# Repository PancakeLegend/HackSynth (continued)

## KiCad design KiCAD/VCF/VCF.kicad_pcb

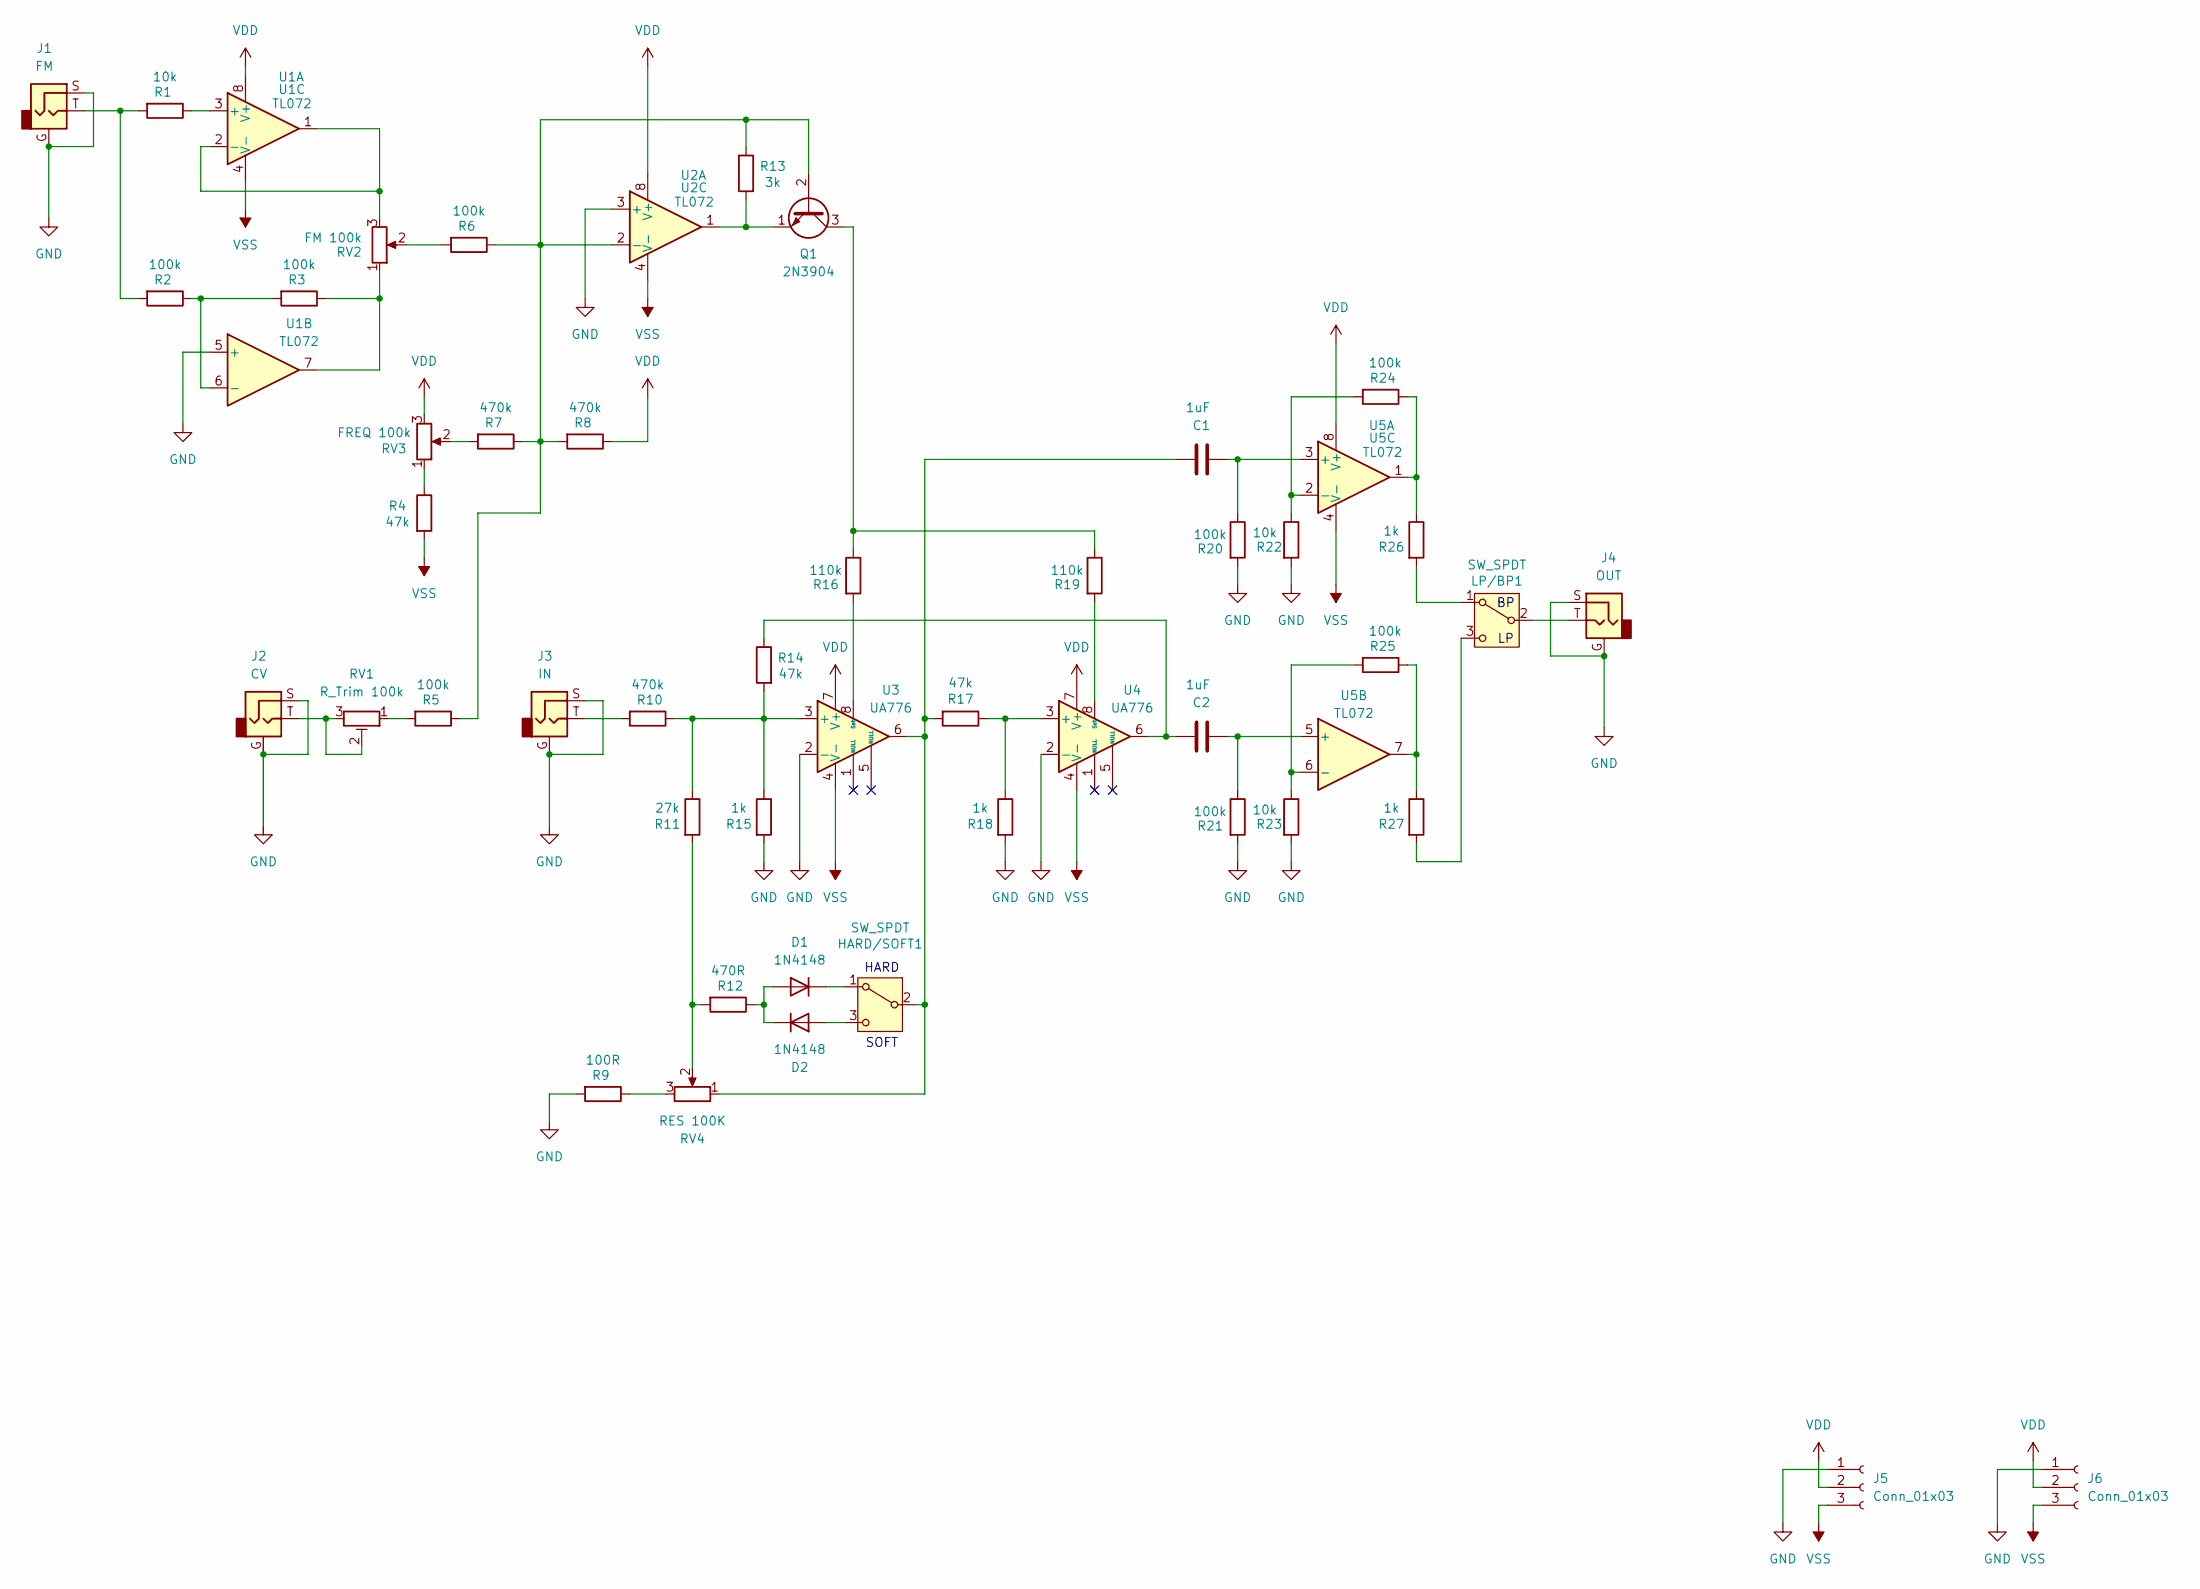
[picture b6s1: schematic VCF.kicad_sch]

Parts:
C1, C2: 1uF; C_Ceramic_D4.5mm_P5.00mm
D1, D2: 1N4148; D_DO-35_SOD27_P7.62mm_Horizontal
HARD/SOFT1: SW_SPDT; Switch SPDT - MTS-102
J1: FM; Jack_3.5mm
J2: CV; Jack_3.5mm
J3: IN; Jack_3.5mm
J4: OUT; Jack_3.5mm
J5, J6: Conn_01x03; JST_PH_S3B-PH-K_1x03_P2.00mm_Horizontal
LP/BP1: SW_SPDT; Switch SPDT - MTS-102
Q1: 2N3904; J172_TO-92_Inline - Handsolder
R1, R22, R23: 10k; R_Axial_DIN0207_L6.3mm_D2.5mm_P7.62mm_Horizontal
R2, R3, R5, R6, R20, R21, R24, R25: 100k; R_Axial_DIN0207_L6.3mm_D2.5mm_P7.62mm_Horizontal
R4, R14, R17: 47k; R_Axial_DIN0207_L6.3mm_D2.5mm_P7.62mm_Horizontal
R7, R8, R10: 470k; R_Axial_DIN0207_L6.3mm_D2.5mm_P7.62mm_Horizontal
R9: 100R; R_Axial_DIN0207_L6.3mm_D2.5mm_P7.62mm_Horizontal
R11: 27k; R_Axial_DIN0207_L6.3mm_D2.5mm_P7.62mm_Horizontal
R12: 470R; R_Axial_DIN0207_L6.3mm_D2.5mm_P7.62mm_Horizontal
R13: 3k; R_Axial_DIN0207_L6.3mm_D2.5mm_P7.62mm_Horizontal
R15, R18, R26, R27: 1k; R_Axial_DIN0207_L6.3mm_D2.5mm_P7.62mm_Horizontal
R16, R19: 110k; R_Axial_DIN0207_L6.3mm_D2.5mm_P7.62mm_Horizontal
RV1: R_Trim 100k; TrimPot_Bourns_3339S_Horizontal
RV2: FM 100k; Potentiometer_Alps_RK09K_Horizontal
RV3: FREQ 100k; Potentiometer_Alps_RK09K_Horizontal
RV4: RES 100K; Potentiometer_Alps_RK09K_Horizontal
U1, U2, U5: TL072; DIP-8_W7.62mm_LongPads
U3, U4: UA776; DIP-8_W7.62mm_LongPads

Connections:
GND: J1.G, J1.S, J2.G, J2.S, J3.G, J3.S, J4.G, J4.S, J5.1, J6.1, R9.2, R15.2, R18.2, R20.2, R21.2, R22.2, R23.2, U1.5 (+), U2.3 (+), U3.2 (-), U4.2 (-)
unnamed: C2.1, R14.1, U4.6
unnamed: D1.2 (A), D2.1 (K), R12.1
unnamed 3: D1.1 (K), HARD/SOFT1.1 (A); also elsewhere on the board
unnamed 4: D2.2 (A), HARD/SOFT1.3 (C); also elsewhere on the board
unnamed 5: C1.1, HARD/SOFT1.2 (B), R17.2, RV4.1, U3.6; also elsewhere on the board
unnamed: J1.T, R1.2, R2.2
unnamed: J2.T, RV1.2, RV1.3
unnamed: J3.T, R10.2
unnamed 9: LP/BP1.1 (A), R26.2; also elsewhere on the board
unnamed 10: J4.T, LP/BP1.2 (B); also elsewhere on the board
unnamed 11: LP/BP1.3 (C), R27.2; also elsewhere on the board
unnamed: Q1.2 (B), R5.1, R6.1, R7.1, R8.2, R13.1, U2.2 (-)
unnamed: Q1.3 (C), R16.1, R19.1
unnamed: Q1.1 (E), R13.2, U2.1
unnamed: R3.1, RV2.1, U1.7
unnamed: R4.1, RV3.1
unnamed: R5.2, RV1.1
unnamed: R6.2, RV2.2
unnamed: R7.2, RV3.2
unnamed: R9.1, RV4.3
unnamed: R11.2, R12.2, RV4.2
unnamed: R24.1, R26.1, U5.1
unnamed: R25.1, R27.1, U5.7
unnamed: R1.1, U1.3 (+)
unnamed: RV2.3, U1.1, U1.2 (-)
unnamed: R2.1, R3.2, U1.6 (-)
unnamed: R10.1, R11.1, R14.2, R15.1, U3.3 (+)
unnamed: R16.2, U3.8 (Set)
unnamed: R17.1, R18.1, U4.3 (+)
unnamed: R19.2, U4.8 (Set)
unnamed: C1.2, R20.1, U5.3 (+)
unnamed: R22.1, R24.2, U5.2 (-)
unnamed: C2.2, R21.1, U5.5 (+)
unnamed: R23.1, R25.2, U5.6 (-)
VDD: J5.2, J6.2, R8.1, RV3.3, U1.8 (V+), U2.8 (V+), U3.7 (V+), U4.7 (V+), U5.8 (V+)
VSS: J5.3, J6.3, R4.2, U1.4 (V-), U2.4 (V-), U3.4 (V-), U4.4 (V-), U5.4 (V-)

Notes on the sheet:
SOFT
HARD

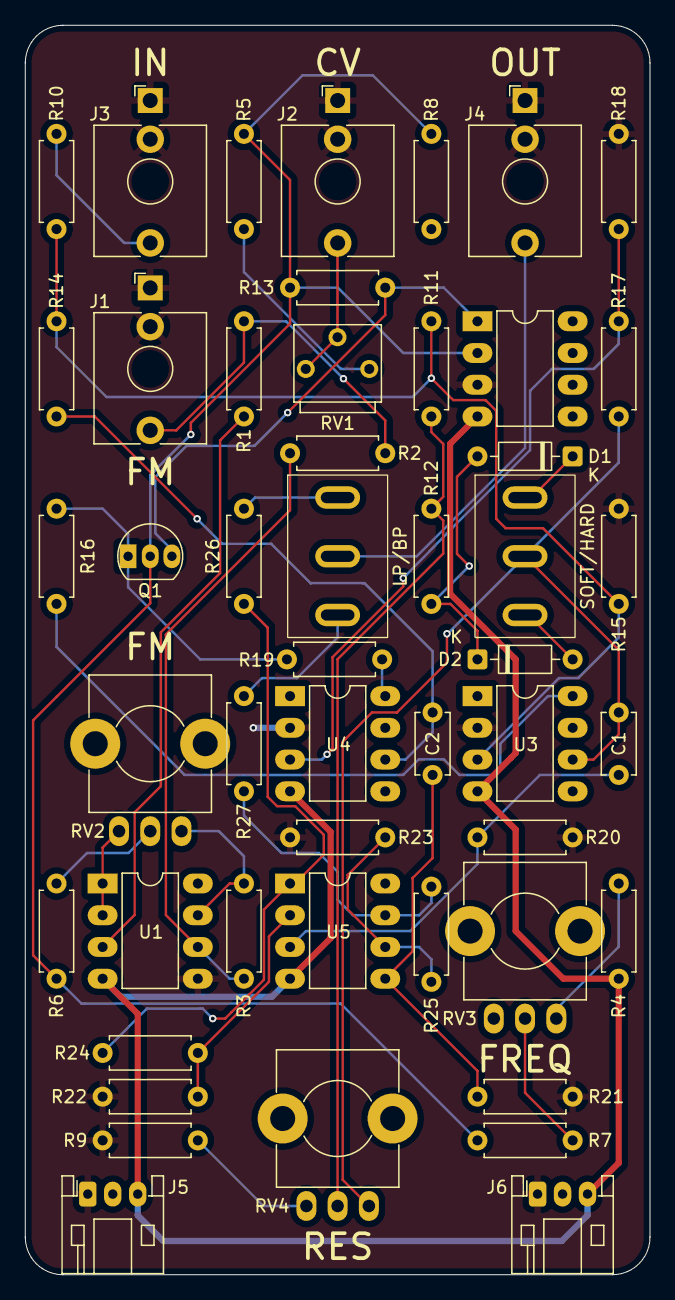
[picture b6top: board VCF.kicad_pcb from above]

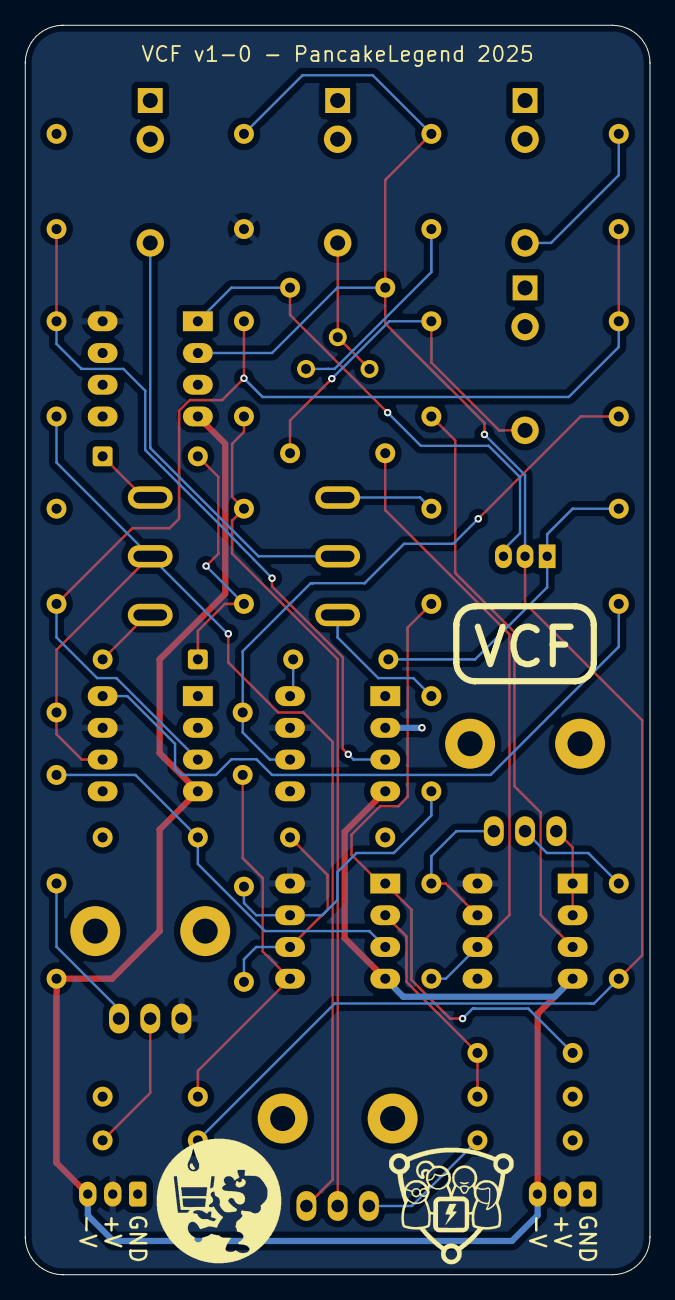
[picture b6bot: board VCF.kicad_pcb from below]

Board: 2 copper layers, 50.0 x 100.0 mm, 51 parts (2 on the bottom side), 37 nets.

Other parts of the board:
LP/BP: SW_SPDT; Switch SPDT - MTS-102
Ref**: Val**; PancakeLegend Logo - 10mm
Ref**#2: Val**; CCHS Logo - 10mm
SOFT/HARD: SW_SPDT; Switch SPDT - MTS-102

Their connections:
unnamed 3: SOFT/HARD.1 (A); also elsewhere on the board
unnamed 4: SOFT/HARD.3 (C); also elsewhere on the board
unnamed 5: SOFT/HARD.2 (B); also elsewhere on the board
unnamed 9: LP/BP.1 (A); also elsewhere on the board
unnamed 10: LP/BP.2 (B); also elsewhere on the board
unnamed 11: LP/BP.3 (C); also elsewhere on the board

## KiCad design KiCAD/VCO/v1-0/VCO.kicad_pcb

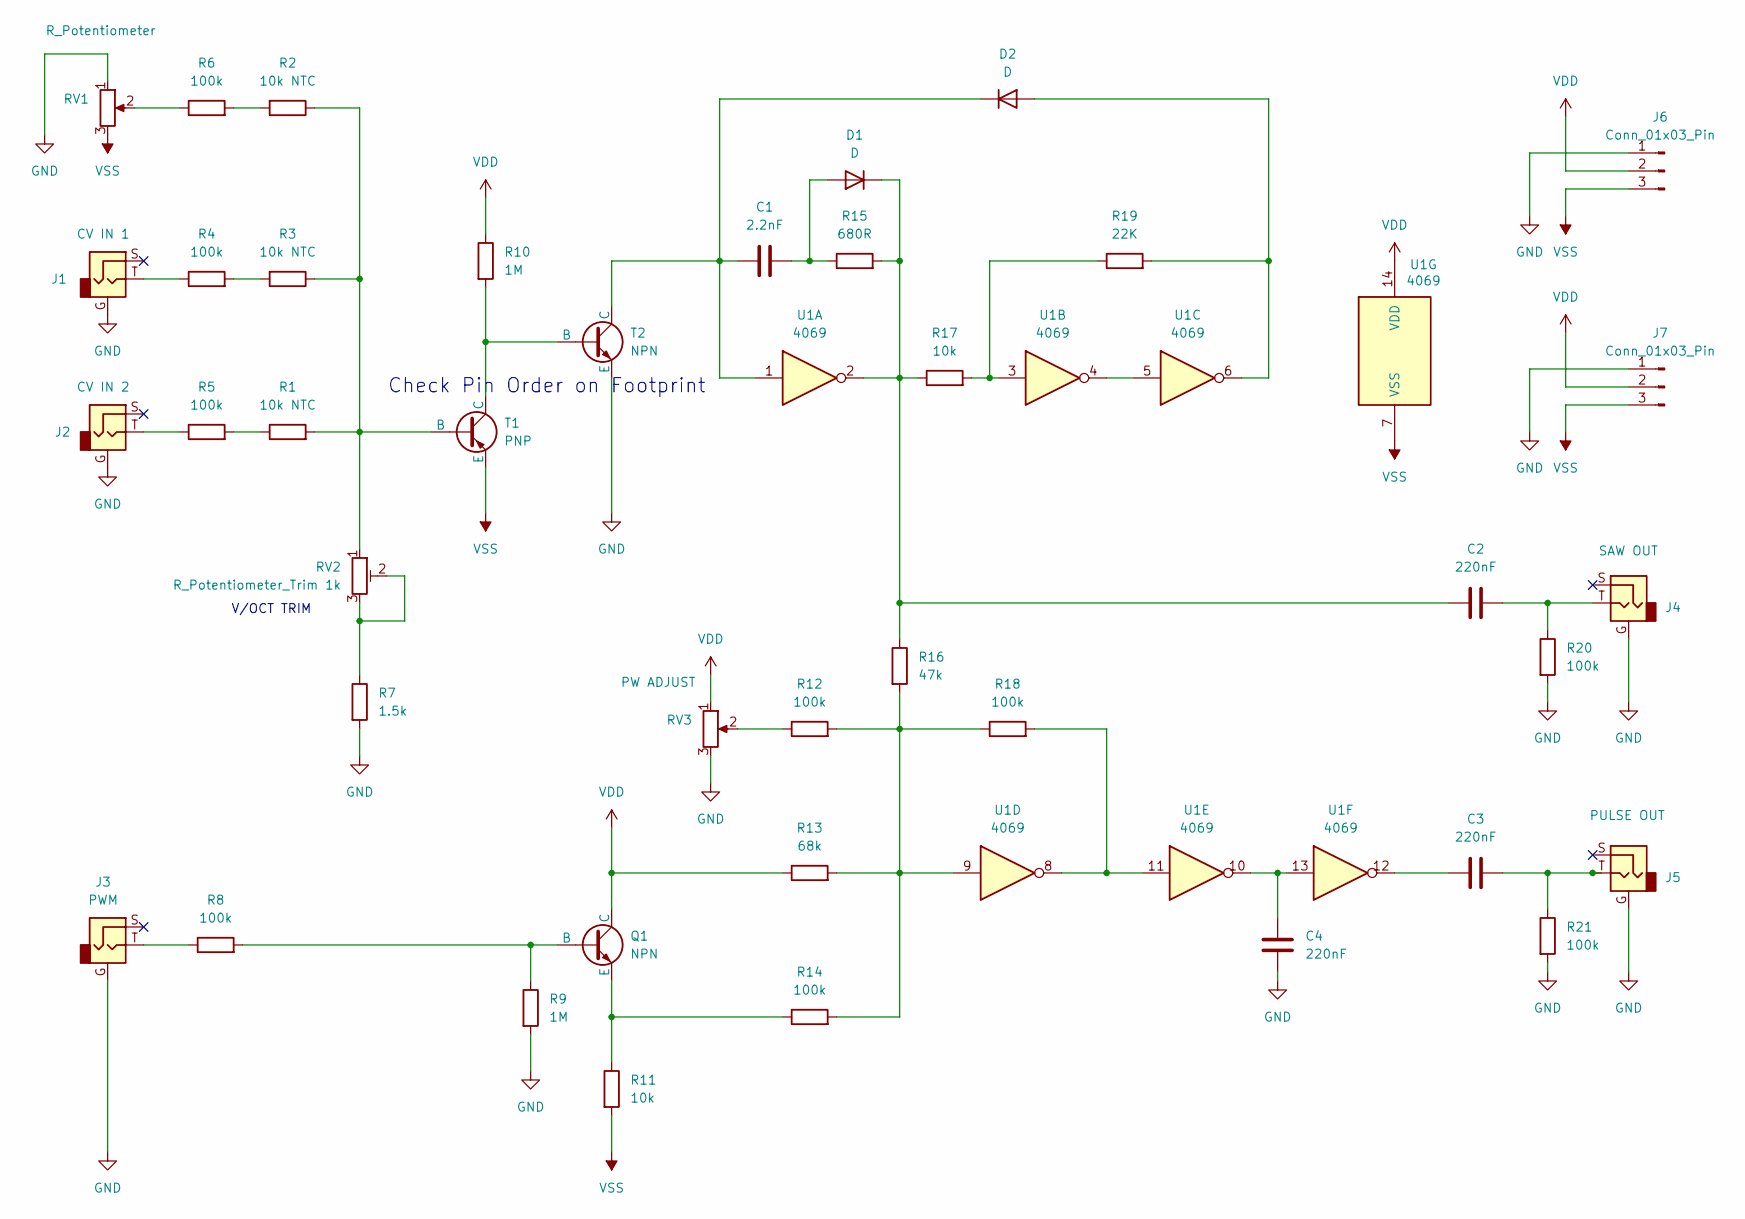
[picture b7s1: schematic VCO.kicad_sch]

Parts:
C1: 2.2nF; C_Disc_D5.0mm_W2.5mm_P2.50mm
C2, C3, C4: 220nF; C_Disc_D5.0mm_W2.5mm_P2.50mm
D1, D2: D; D_A-405_P7.62mm_Horizontal
J1: CV IN 1; Jack_3.5mm
J2: CV IN 2; Jack_3.5mm
J3: PWM; Jack_3.5mm
J4: SAW OUT; Jack_3.5mm
J5: PULSE OUT; Jack_3.5mm
J6, J7: Conn_01x03_Pin; JST_PH_S3B-PH-K_1x03_P2.00mm_Horizontal
Q1: NPN; TO-92_Inline - Handsolder
R1, R2, R3: 10k NTC; R_Axial_DIN0207_L6.3mm_D2.5mm_P2.54mm_Vertical
R4, R5, R6, R8, R12, R14, R18, R20, R21: 100k; R_Axial_DIN0207_L6.3mm_D2.5mm_P7.62mm_Horizontal
R7: 1.5k; R_Axial_DIN0207_L6.3mm_D2.5mm_P7.62mm_Horizontal
R9, R10: 1M; R_Axial_DIN0207_L6.3mm_D2.5mm_P7.62mm_Horizontal
R11, R17: 10k; R_Axial_DIN0207_L6.3mm_D2.5mm_P7.62mm_Horizontal
R13: 68k; R_Axial_DIN0207_L6.3mm_D2.5mm_P7.62mm_Horizontal
R15: 680R; R_Axial_DIN0207_L6.3mm_D2.5mm_P7.62mm_Horizontal
R16: 47k; R_Axial_DIN0207_L6.3mm_D2.5mm_P7.62mm_Horizontal
R19: 22K; R_Axial_DIN0207_L6.3mm_D2.5mm_P7.62mm_Horizontal
RV1: R_Potentiometer; Potentiometer_Alps_RK09K_Horizontal
RV2: R_Potentiometer_Trim 1k; TrimPot_Bourns_3339S_Horizontal
RV3: PW ADJUST; Potentiometer_Alps_RK09K_Horizontal
T1: PNP; TO-92_Inline - Handsolder
T2: NPN; TO-92_Inline - Handsolder
U1: 4069; DIP-14_W7.62mm_LongPads

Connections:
GND: C4.1, J1.G, J2.G, J3.G, J4.G, J5.G, J6.1, J7.1, R7.2, R9.2, R20.2, R21.2, RV1.1, RV3.3, T2.3 (E)
unnamed: C2.2, J4.T, R20.1
unnamed: C3.1, U1.12
unnamed: C3.2, J5.T, R21.1
unnamed: C4.2, U1.10, U1.13
unnamed: C1.2, D1.2 (A), R15.1
unnamed: C2.1, D1.1 (K), R15.2, R16.1, R17.1, U1.2
unnamed: D2.2 (A), R19.2, U1.6
unnamed: C1.1, D2.1 (K), T2.1 (C), U1.1
unnamed: J1.T, R4.1
unnamed: J2.T, R5.1
unnamed: J3.T, R8.1
unnamed: Q1.2 (B), R8.2, R9.1
unnamed: Q1.3 (E), R11.1, R14.1
unnamed: R1.1, R5.2
unnamed: R2.2, R6.2
unnamed: R3.2, R4.2
unnamed: R6.1, RV1.2
unnamed: R7.1, RV2.2, RV2.3
unnamed: R12.1, RV3.2
unnamed: R12.2, R13.2, R14.2, R16.2, R18.1, U1.9
unnamed: R17.2, R19.1, U1.3
unnamed: R18.2, U1.8, U1.11
unnamed: R1.2, R2.1, R3.1, RV2.1, T1.2 (B)
unnamed: R10.2, T1.1 (C), T2.2 (B)
unnamed: U1.4, U1.5
VDD: J6.2, J7.2, Q1.1 (C), R10.1, R13.1, RV3.1, U1.14 (VDD)
VSS: J6.3, J7.3, R11.2, RV1.3, T1.3 (E), U1.7 (VSS)

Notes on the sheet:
Check Pin Order on Footprint
V/OCT TRIM

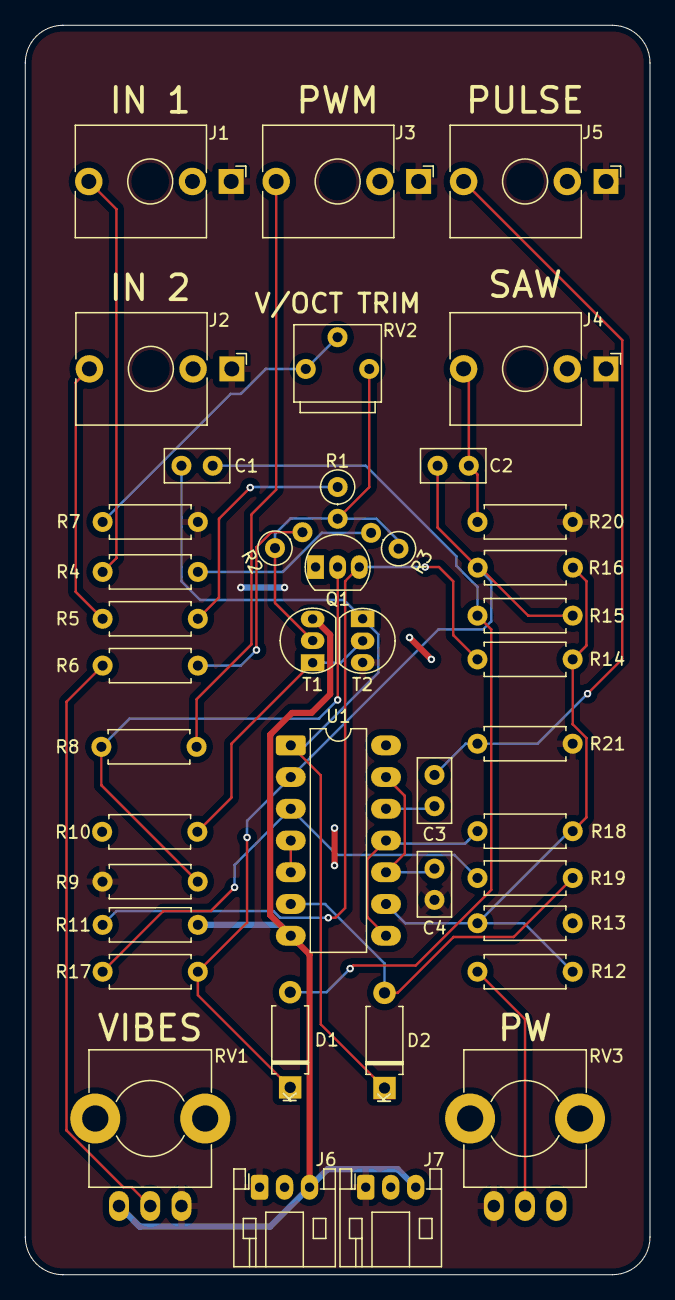
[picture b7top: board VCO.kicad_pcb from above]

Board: 2 copper layers, 50.0 x 100.0 mm, 41 parts (0 on the bottom side), 28 nets.
